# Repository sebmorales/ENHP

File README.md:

# Networked Hardware- Getting Started

Woo! You got your board on the mail, or maybe we gave it to you in person, now, what is it? What is it for?

This board is based on a ESP32 microcontroller, but it also has some other components to help us get started connecting the digital world and our tangible one. We will go more in depth during class, but for now, here is a quick manual to get you going. 

By default, the board is already pre-programmed, so you don’t have to worry about that. But if you want to make changes, you are more than welcome to do so. We will soon update this same doc to share the code and schematics.

*Note: The board in a bit of an experimental stage and we are still trying to figure things out, so please share any feedback and bugs as you find them :)*

Each board has a unique name (written by hand on the back of the board). Let’s get the boards connected and start sharing light data!

If you go to the webpage [https://hardwaremovement.com](https://hardwaremovement.com) you will see a grid of boxes, each with a name. At the time I took this image, there were only three boards on there, hopefully by now there are many more. As new boards connect, the grid starts getting updated with each boards' last photoresistor reading. 

This website is only collecting light information, and since other people will likely connect at different times, feel free to come back and see how the collaborative page is changing over time. Feel free to place the board anywhere indoors and see how that impacts the page. 

## Let’s connect!

### How to connect the board to wifi [video]

[https://vimeo.com/725318091](https://vimeo.com/725318091)

### How to connect the board to wifi step by step

1. Turn on the switch on the ESP32 board. 
    1. You will hear a click (that's the relay acting as a small audio cue)
    2. You will see the board blink about 1x a second, this means that the board is attempting to connect to a wifi network. But because you just got the board it will most likely not be able to connect.

2. If after 15 seconds it wasn’t able to connect:
    1. The board will beep again
    2. The LED will start blinking at a faster pace (2x second)
    3. It will then make its own wifi network. You can connect to it to share your wifi credentials. You can do this either though your phone or computer’s wifi settings. 
    
    The name of the network will be *ExperimentHardPerf_[random numbers]*

1. After 5-10 seconds a login page (captive portal) will show up on your device. 

Note: watch out for upper/lower case

1. Enter your wifi info then click save (Note: watch out for upper/lower case)

Note: watch out for upper/lower case

1. Once you click save, the board will attempt to connect to your network. It will also save your network credentials to it’s internal memory, so you don’t have to add them again (unless you change them). You can now press cancel>use other network, and connect to your regular wifi.

1. If the connection is successful, you will see a quick short flashing LED. Then then you can check the [https://hardwaremovement.com](https://hardwaremovement.com)  website again and see it updating live! The board should then go to sleep and automatically wake up every 20 minutes until it rans out of battery in about a day. If you want, you can charge it again or leave it plugged in. 

### Trouble shooting

- I turn it on but nothing happens, no beep, no flashing led.
    
    Most likely, it’s out of battery, try charging it though the micro USB port
    
- I turn the board on, and it beeps, then it beeps again, and again, and again…
    
    This means that the board is constantly restarting, most likely it’s out of battery, try recharging the battery though it’s Micro USB port
    
- I added my wifi credentials but doesn’t nothing happened.
    
    Try restarting the board by turning it off and on again, the board should attempt to connect and if it still is not able, repeat steps 2-6.
    
    Also, in order to save battery, it will only wait for 1minute before going back to sleep. It could be that it’s taking a bit long to add your wifi credentials.
    
- I was able to connect before now it’s asking for my wifi credentials again
    
    The board only has 15 seconds to successfully connect to wifi, after this it will create it’s own network. Sometimes, these 15 seconds are not enough time connect, no need to add you credentials again, you can restart the board and have it try again. 

---

### Additional info: Getting familiar with the board

The board consists of the micocontroller ([ESP32 dev board with a 18650 battery holder](https://wiki.geekworm.com/index.php/WEMOS_ESP32_Board_with_18650_Battery_Holder)) and a series of inputs and outputs:

### **Inputs:**

- **Photoresistor**- This can be used to sense light
- **Magnetometer**- This is the ([MMC5603NJ](mages/MMC5603NJ.pdf)), a 3 axis magnetic + temperature sensor
- **Potentiometer**- This is a knob can be manually turned
- **Button-** This button has a dual function, to send data while the board is awake, and to wake the board when it is sleeping

### **Outputs:**

- **Relay**- Instead of having a buzzer that could only buzz, we upgraded it to a full size relay, it clicks and it switches! We recomend only using it for DC applications, but if you know what you are doing feel free. 
- **An LED output and pin-** this can be used to see changes or to connect to another board or arduino.
- **A Servo-** this can be used to move things in our physical, it can turn about 180°.

### **COM:**
- **I2C**- This uses a STEMMA QT connector, a popular i2C compatible with many Adafruit and Sparkfun modules.
- **RXTX**- These are ready in case you want to connect to another micrcontroller or anything that can communicate though serial. By default the board runs on a 115200 buadrate and only supports 3.3V.
- **GPIO 17 & 18**- By defualt 17 is set to be a digital input (0-1) and 18 is set as an analog out (0-255).
### Power

- The ESP32 board has a switch to turn it on/off
- It can be charged/programmed using a micro USB cable
- We added a small switch to let you decide if the board should stay connected or if it should connect every 20 minutes and then go to sleep. This will dramatically impact how long the board can run on battery.

## Check out [MORAKANA.COM](https://morakana.com/work/networked-hardware2.0) for more details and examples.

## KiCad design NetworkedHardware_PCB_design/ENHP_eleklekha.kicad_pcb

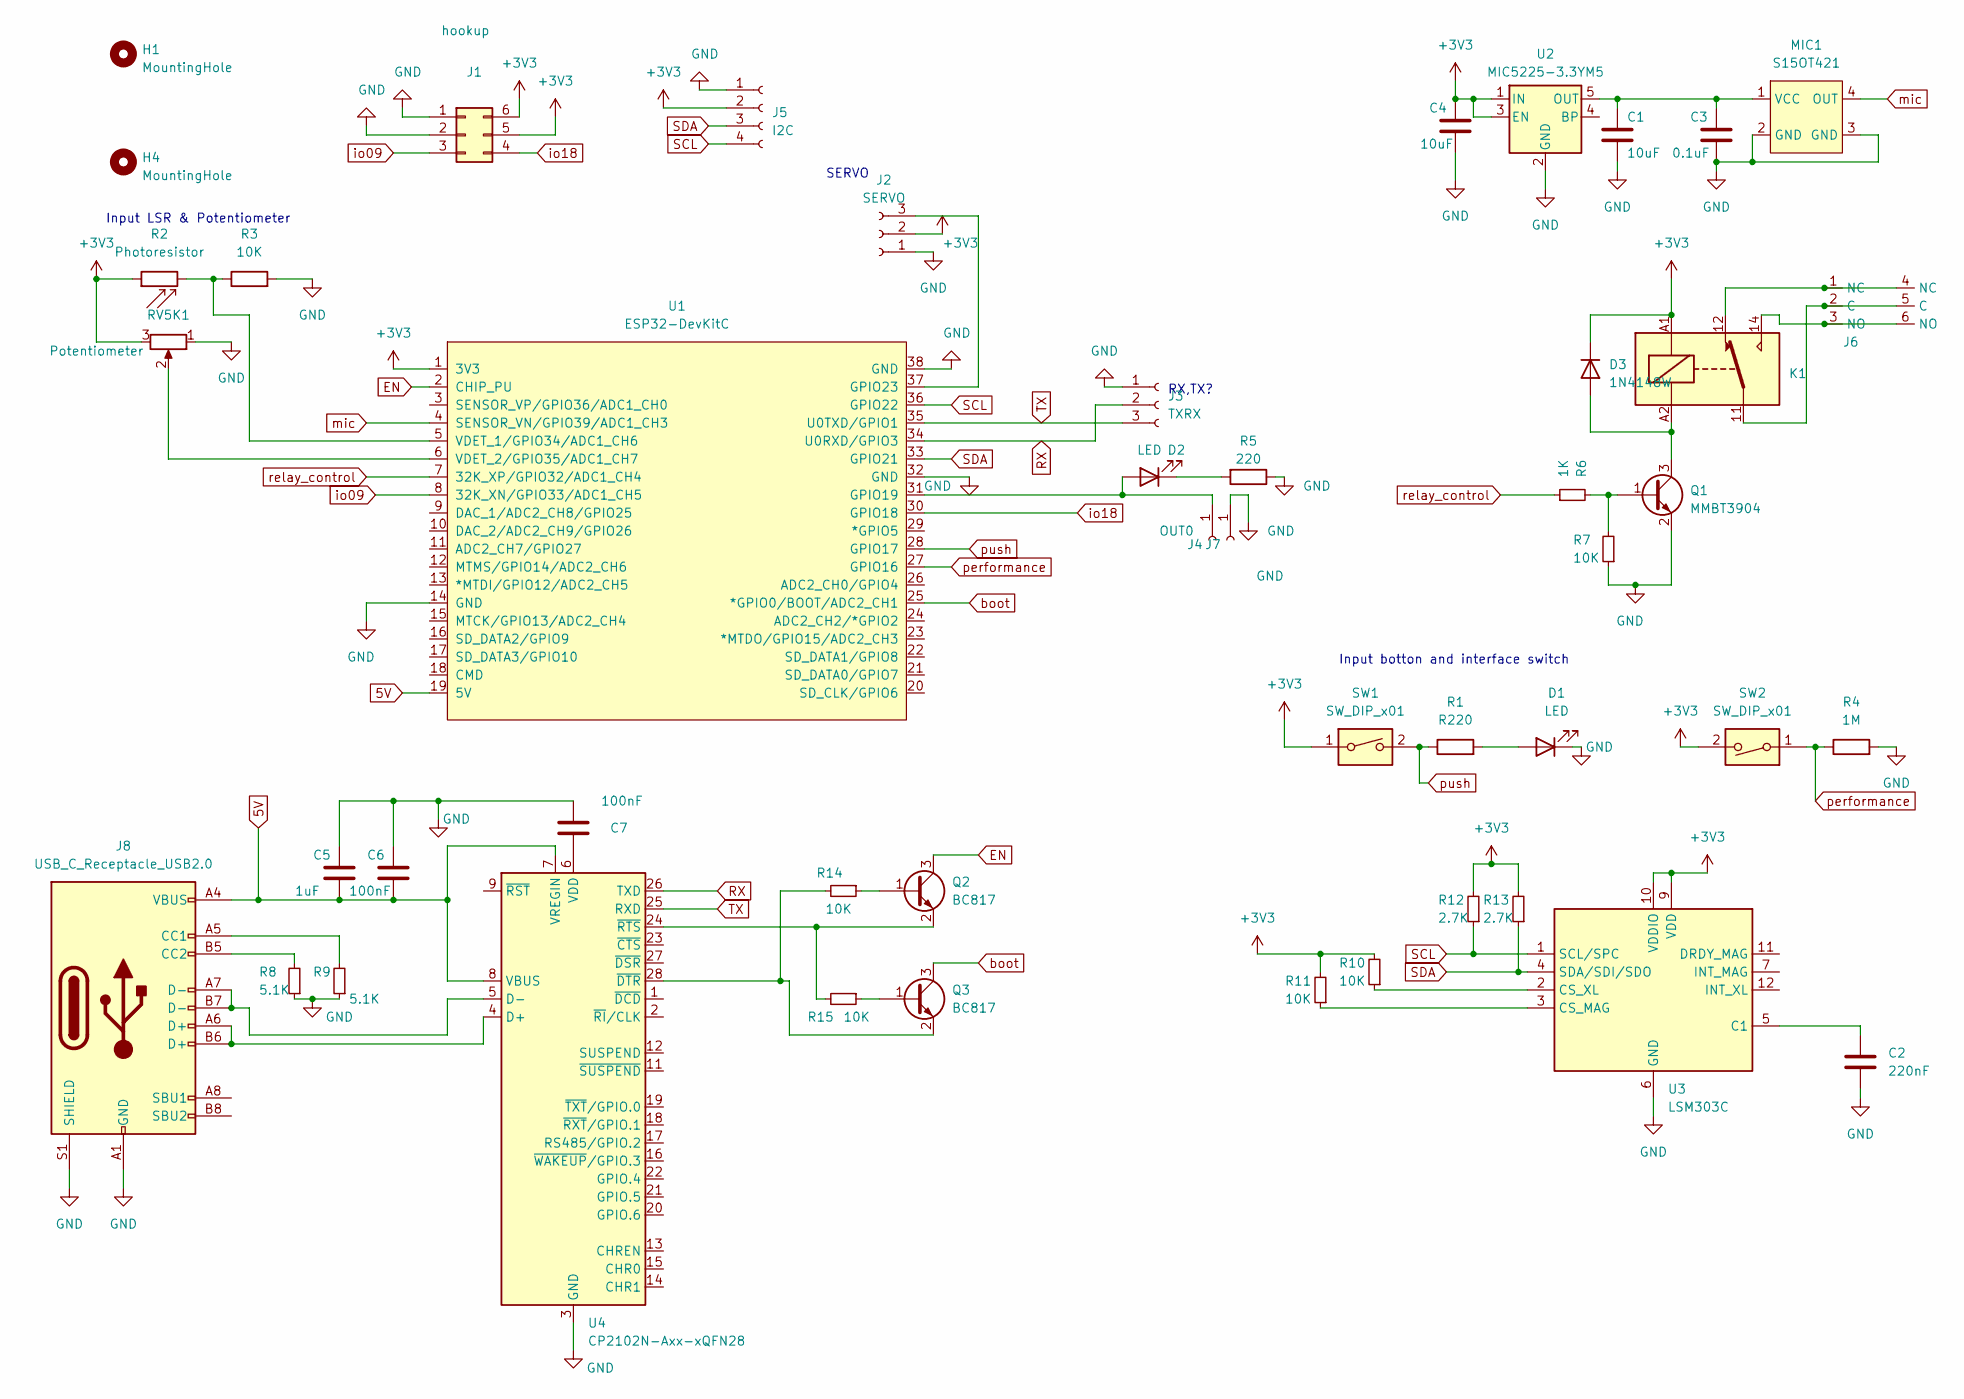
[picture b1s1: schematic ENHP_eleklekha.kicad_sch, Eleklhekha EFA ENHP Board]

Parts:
C1, C4: 10uF; C_0805_2012Metric
C2: 220nF; C_0805_2012Metric
C3: 0.1uF; C_0805_2012Metric
C5: 1uF; C_0805_2012Metric
C6, C7: 100nF; C_0805_2012Metric
D1, D2: LED; LED_0805_2012Metric_Pad1.15x1.40mm_HandSolder
D3: 1N4148W; D_SOD-123
H1, H4: MountingHole; MountingHole_2.5mm_Pad_TopBottom
J1: hookup; PinSocket_2x03_P2.54mm_Vertical
J2: SERVO; PinSocket_1x03_P2.54mm_Vertical
J3: TXRX; PinHeader_1x03_P2.54mm_Vertical
J4: OUT0; SolderWire-0.5sqmm_1x01_D0.9mm_OD2.1mm
J5: I2C; JST_SH_SM04B-SRSS-TB_1x04-1MP_P1.00mm_Horizontal
J6: spring_terminal
J7: GND; SolderWire-0.5sqmm_1x01_D0.9mm_OD2.1mm
J8: USB_C_Receptacle_USB2.0; USB_C_Receptacle_Amphenol_12401610E4-2A_CircularHoles
K1: FINDER-36.11; Relay_SPDT_Finder_36.11
MIC1: S15OT421; JLC C2684419
Q1: MMBT3904; SOT-23
Q2, Q3: BC817; SOT-23
R1: R220; R_0805_2012Metric_Pad1.20x1.40mm_HandSolder
R2: Photoresistor; R_Axial_DIN0204_L3.6mm_D1.6mm_P2.54mm_Vertical
R3, R7, R10, R11, R14, R15: 10K; R_0805_2012Metric_Pad1.20x1.40mm_HandSolder
R4: 1M; R_0805_2012Metric_Pad1.20x1.40mm_HandSolder
R5: 220; R_0805_2012Metric_Pad1.20x1.40mm_HandSolder
R6: 1K; R_0805_2012Metric_Pad1.20x1.40mm_HandSolder
R8, R9: 5.1K; R_0805_2012Metric_Pad1.20x1.40mm_HandSolder
R12, R13: 2.7K; R_0805_2012Metric_Pad1.20x1.40mm_HandSolder
RV5K1: Potentiometer; Potentiometer_Bourns_PTV09A-1_Single_Vertical
SW1: SW_DIP_x01; SW_Push_1P1T_NO_CK_KSC7xxJ
SW2: SW_DIP_x01; SW_DIP_SPSTx01_Slide_Omron_A6S-110x_W8.9mm_P2.54mm
U1: ESP32-DevKitC; ESP32-Dev_Batt_18650
U2: MIC5225-3.3YM5; SOT-23-5; JLC C512101
U3: LSM303C; LGA-12_2x2mm_P0.5mm
U4: CP2102N-Axx-xQFN28; QFN-28-1EP_5x5mm_P0.5mm_EP3.35x3.35mm

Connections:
5V: C5.2, C6.2, J8.A4 (VBUS), J8.A9 (VBUS), J8.B4 (VBUS), J8.B9 (VBUS), U1.19 (5V), U4.7 (VREGIN), U4.8 (VBUS)
+3V3: C4.2, D3.1 (K), J1.5, J1.6, J2.2, J5.2, K1.A1, R2.1, R10.2, R11.2, R12.2, R13.2, RV5K1.3, SW1.1, SW2.2, U1.1 (3V3), U2.1 (IN), U2.3 (EN), U3.9 (VDD), U3.10 (VDDIO)
EN: Q2.3 (C), U1.2 (CHIP_PU)
GND: C1.1, C2.2, C3.2, C4.1, C5.1, C6.1, C7.1, D1.1 (K), J1.1, J1.2, J2.1, J3.1, J5.1, J7.1, J8.A1 (GND), J8.A12 (GND), J8.B1 (GND), J8.B12 (GND), J8.S1 (SHIELD), MIC1.2 (GND), MIC1.3 (GND), Q1.2 (E), R3.2, R4.2, R5.1, R7.1, R8.1, R9.1, RV5K1.1, U1.14 (GND), U1.32 (GND), U1.38 (GND), U2.2 (GND), U3.6 (GND), U3.8 (GND), U4.3 (GND), U4.29 (GND); also elsewhere on the board
unnamed: D1.2 (A), R1.2
unnamed: D2.2 (A), J4.1, U1.31 (GPIO19)
unnamed: D2.1 (K), R5.2
unnamed: D3.2 (A), K1.A2, Q1.3 (C)
unnamed: J2.3, U1.37 (GPIO23)
unnamed: J6.2 (C), J6.5 (C), K1.11
unnamed: J6.1 (NC), J6.4 (NC), K1.12
unnamed: J6.3 (NO), J6.6 (NO), K1.14
unnamed: J8.A5 (CC1), R9.2
unnamed: J8.B5 (CC2), R8.2
unnamed 14: C1.2, C3.1, MIC1.1 (VCC), U2.5 (OUT); also elsewhere on the board
unnamed: Q1.1 (B), R6.2, R7.2
unnamed: Q2.1 (B), R14.1
unnamed: Q2.2 (E), R15.2, U4.24 (~RTS)
unnamed: Q3.1 (B), R15.1
unnamed: Q3.2 (E), R14.2, U4.28 (~DTR)
unnamed: R2.2, R3.1, U1.5 (VDET_1/GPIO34/ADC1_CH6)
unnamed: RV5K1.2, U1.6 (VDET_2/GPIO35/ADC1_CH7)
unnamed: C2.1, U3.5 (C1)
unnamed: R11.1, U3.3 (CS_MAG)
unnamed: R10.1, U3.2 (CS_XL)
unnamed: J8.A6 (D+), J8.B6 (D+), U4.4 (D+)
unnamed: J8.A7 (D-), J8.B7 (D-), U4.5 (D-)
unnamed: C7.2, U4.6 (VDD)
RX: J3.2, U1.34 (U0RXD/GPIO3), U4.26 (TXD)
SCL: J5.4, R12.1, U1.36 (GPIO22), U3.1 (SCL/SPC)
SDA: J5.3, R13.1, U1.33 (GPIO21), U3.4 (SDA/SDI/SDO)
TX: J3.3, U1.35 (U0TXD/GPIO1), U4.25 (RXD)
boot: Q3.3 (C), U1.25 (*GPIO0/BOOT/ADC2_CH1)
io09: J1.3, U1.8 (32K_XN/GPIO33/ADC1_CH5)
io18: J1.4, U1.30 (GPIO18)
mic: MIC1.4 (OUT), U1.4 (SENSOR_VN/GPIO39/ADC1_CH3); also elsewhere on the board
performance: R4.1, SW2.1, U1.27 (GPIO16)
push: R1.1, SW1.2, U1.28 (GPIO17)
relay_control: R6.1, U1.7 (32K_XP/GPIO32/ADC1_CH4)

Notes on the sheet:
Input LSR & Potentiometer
SERVO
Input botton and interface switch
RX,TX?

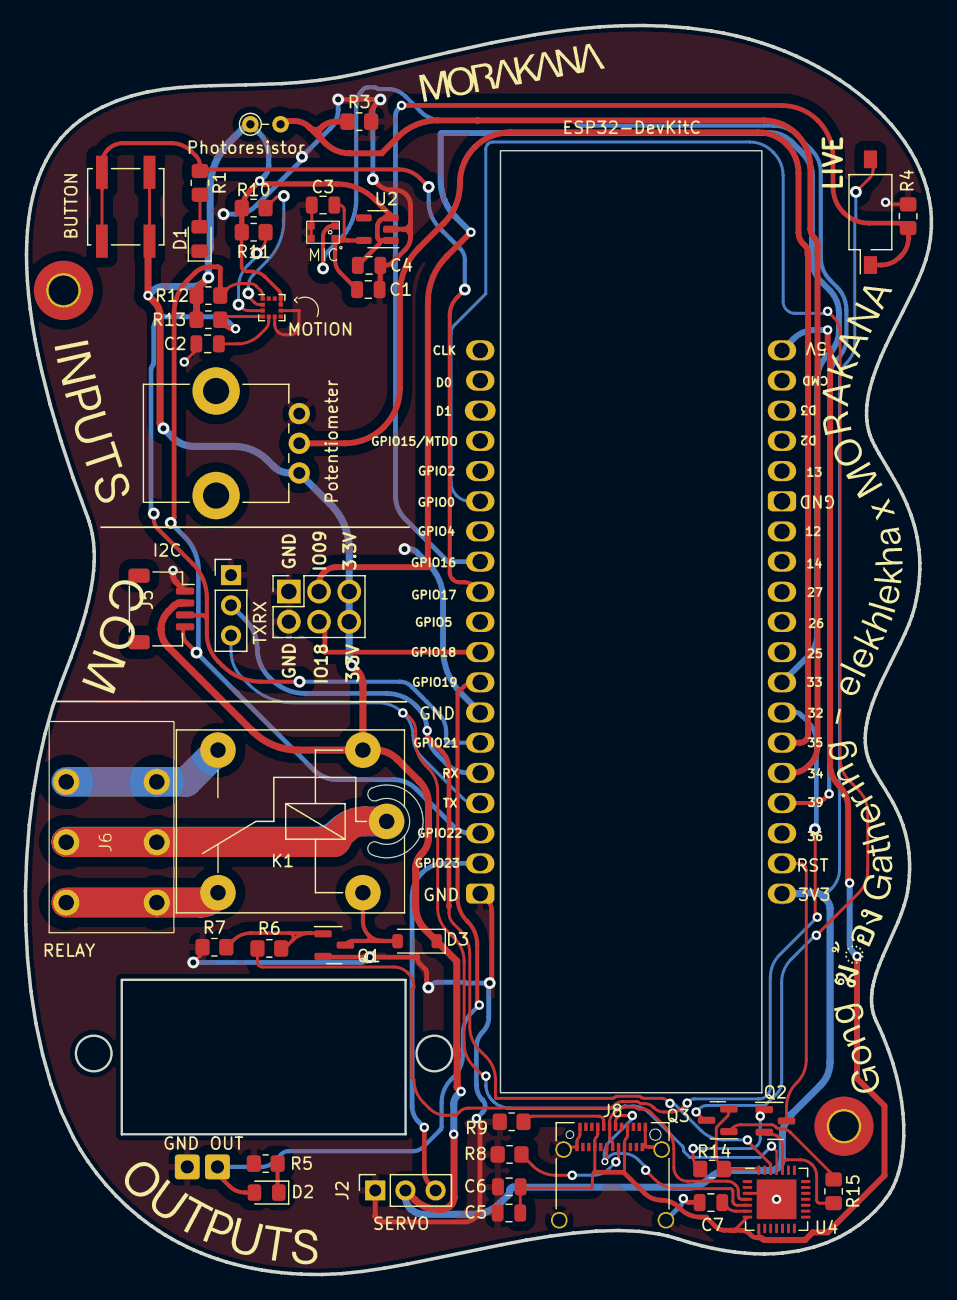
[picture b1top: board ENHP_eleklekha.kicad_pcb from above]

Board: 2 copper layers, 76.3 x 105.1 mm, 47 parts (0 on the bottom side), 39 nets.

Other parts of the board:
MIC: S15OT421

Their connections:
GND: MIC.2 (GND), MIC.3 (GND); also elsewhere on the board
unnamed 14: MIC.1 (VCC); also elsewhere on the board
mic: MIC.4 (OUT); also elsewhere on the board

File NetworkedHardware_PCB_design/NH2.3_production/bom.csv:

Designator,Footprint,Quantity,Value,LCSC Part #
"C1, C4",0805,2,10uF,
C2,0805,1,220nF,
C3,0805,1,0.1uF,
C5,0805,1,1uF,
"C6, C7",0805,2,100nF,
"D1, D2",0805,2,LED,
D3,D_SOD-123,1,1N4148W,
"H1, H3, H4",MountingHole_2.5mm_Pad_TopBottom,3,MountingHole,
J1,PinSocket_2x03_P2.54mm_Vertical,1,hookup,
J2,PinSocket_1x03_P2.54mm_Vertical,1,SERVO,
J3,PinHeader_1x03_P2.54mm_Vertical,1,TXRX,
J4,SolderWire-0.5sqmm_1x01_D0.9mm_OD2.1mm,1,OUT0,
J5,JST_SH_SM04B-SRSS-TB_1x04-1MP_P1.00mm_Horizontal,1,I2C ,
J6,spring_terminal,1,~,
J7,SolderWire-0.5sqmm_1x01_D0.9mm_OD2.1mm,1,GND,
J8,USB_C_Receptacle_Amphenol_12401610E4-2A_CircularHoles,1,USB_C_Receptacle_USB2.0,
K1,Relay_SPDT_Finder_36.11,1,FINDER-36.11,
Q1,SOT-23,1,MMBT3904,
"Q2, Q3",SOT-23,2,BC817,
R1,0805,1,R220,
"R10, R11, R14, R15, R3, R7",0805,6,10K,
"R12, R13",0805,2,2.7K,
R2,R_Axial_DIN0204_L3.6mm_D1.6mm_P2.54mm_Vertical,1,Photoresistor,
R4,0805,1,1M,
R5,0805,1,220,
R6,0805,1,1K,
"R8, R9",0805,2,5.1K,
RV5K1,Potentiometer_Bourns_PTV09A-1_Single_Vertical,1,Potentiometer,
SW1,SW_Push_1P1T_NO_CK_KSC7xxJ,1,SW_DIP_x01,
SW2,SW_DIP_SPSTx01_Slide_Omron_A6S-110x_W8.9mm_P2.54mm,1,SW_DIP_x01,
U1,ESP32-Dev_Batt_18650,1,ESP32-DevKitC,
U2,SOT-23-5,1,MIC5225-3.3YM5,C512101
U3,LGA-12_2x2mm_P0.5mm,1,LSM303C,
U4,QFN-28-1EP_5x5mm_P0.5mm_EP3.35x3.35mm,1,CP2102N-Axx-xQFN28,

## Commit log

2022-07-01 Add files via upload
    Initial commit
2022-07-01 Add files via upload
    Initial server commit
2022-07-06 images for readme
2022-07-06 initial Readme
2022-07-06 fixed image hardwaremovement page
2022-07-09 Fixed bugs detected in class
    Fixed:
    * Added board name to network name
    * Fixed MQTT Connection ID
    * Fixed error sharing network names with spaces in them " ".
2022-07-11 Add files via upload
    added connection retry if it had already successfully connected.
2023-06-19 MMC5603NJ 3 axis low cost magnetic sensor
    added datasheet
2023-06-19 Networked Hardware2.0
    Hand holding board
2023-06-19 Update README.md
    Updated to Version 2.0
2023-06-19 Updated to 2023 version
    Added magnetic sensor, relay, and improved general flow.
2023-06-24 KiCad files
    Uploaded design files for circuit board.
2023-06-24 added kicad image
2023-07-03 sonify and playback
    sonified sketch and added playback history feature
2023-07-03 added html for playback sketch
2023-07-03 updated server for 2023 class
2024-01-06 Updated for LSM303
    I replaced the magnetometer to the LSM303 which is better and more accessible. Also added a mic.
2024-01-06 Delete ENHP_ESP32_code/ExpInHardPef/MAG_MMC5603.ino
    replaced for LSM303
2024-01-18 Added production files
    this new 2.3 version includes USB-C charging and programming, this in hopes to relieve the strain on the micro usb port on the esp32 board
2024-01-18 Removed old versions
2024-01-21 updated code for easier user changes
    Made variables like network, mqtt broker, and debugging more accessible
2024-09-15 updated code for elekhlekha
    Adjusted mic sensitivity
    moved ssid and pass to secrets tab
2024-09-15 USB C serial update
    updated PCB design to fix USB C Serial
